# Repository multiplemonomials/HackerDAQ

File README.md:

# HackerDAQ: A Data Acquisition System for Hackers

HackerDAQ is a work-in-progress project to create an open-source data acquisition system. The project is currently in its early stages, but the goal is to create something that can be used in place of industrial DAQ systems to record high-quality data.

## Background and Motivation

The tech industry is in kind of a weird place when it comes to data acquisition (DAQ) systems. Suppose you have some sort of mechanical system you want to work with -- maybe a science experiment, maybe an industrial process, maybe an automation system, who knows. You have some sensors that you need to read and record the data from, and maybe you want to control some outputs as well, like turning the power on to some valves/solenoids/motors in response to a sensor reading. To do this, you need a DAQ system. However, an odd divide exists in the DAQ industry right now, between the incredibly professional and the almost insultingly hobbyist.

At one end of the spectrum, there are industrial-grade offerings from companies like National Instruments, Beckhoff, and Dewesoft. These systems are capable, flexible, and reliable -- but also extremely expensive. Even an entry-level NI system will run you well into the mid 4 figures, and other manufacturers are similar or worse. What if you can't afford that? Well, in many cases, your only option is getting an Arduino or Raspberry Pi and some basic dev boards for the sensors you need, and then hacking together enough software to log the data over serial. I've seen this many times, and while it does sometimes work, by doing it, you give up a lot of niceties like defined accuracy, noise resistance, a constant sample rate, etc.

Meanwhile, technology has moved on, and we're now in an era where highly accurate, multi-input Analog-Digital Converter (ADC) chips can be purchased very cheaply. This project has selected the [AD7770](https://www.analog.com/en/products/ad7770.html) from Analog Devices, a 21-bit, 32kHz, 8-input ADC which can be purchased for about $15 each at quantity. Using this chip enables DAQ devices to be made quite simply and cheaply, as one basically just needs to attach different front-ends to this chip to convert the signals based on the sensor being sampled. With the existence of this chip and others like it, there is really no justification for DAQ devices to cost thousands of dollars unless you need better accuracy or sampling rate than these types of ADCs can provide.

## Basic Overview

The HackerDAQ consists of a main board with a microcontroller on it and basic circuitry such as power supplies, an Ethernet port, and a MicroSD slot. The main board would have a number of connectors for cards to plug in, each of which carries power, GPIOs, and SPI bus signals.

Cards can be designed for many different applications, including digital I/O and many different types of analog sensors. The user can select only the cards they need for the application they have in mind, keeping the base cost of the system down and allowing the user to get exactly the I/O they need. The SPI bus was selected for communications with these cards as it is fast, there are a wide range of chips available that speak it, and it supports bussing together multiple chips on the card over one set of bus lines. In a lot of ways, these cards are similar to existing sensor interconnect systems like SparkFun Qwiic / Adafruit Stemma / Digilent Pmod, where you can buy various task-specific modules and connect them to a motherboard. This would just be focused more on DAQ stuff and be more industrial-grade.

In terms of software, the HackerDAQ would include firmware that would run on the board and interface with all the cards, send data to connected user interface(s), and receive and execute commands. On the PC side, there would be a basic program that can display and record data. For users who don't want to program, they can see the live data in the GUI, record it to a file, and manually control outputs. For users who are a little more comfortable with programming, they could write scripts (likely python) that would run on the host machine and be able to control the DAQ. And for users who have embedded software experience, they could write their own code that extends or replaces the firmware on the actual DAQ!

## Key Decisions

| Area | Decision | Why |
|------------|-------------|--------------|
|Physical architecture | Main board + swappable cards | <ul><li>Avoids need to create multi-function inputs which would increase complexity</li><li>Makes system cheaper if you only need a few types of inputs</li><li>Avoids need to mess around with external amplifiers or other circuitry for sensors that need them -- they can be built directly into the card</li><li>Allows for much wider range of off-the-shelf supported functionality</li></ul>|
|CPU|NXP MCX Alpha Microcontroller running Mbed OS|<ul><li>Using a microcontroller, rather than a linux CPU + supporting circuitry, keeps the cost down</li><li>Using an RTOS rather than a full OS makes microsecond-level timestamping and SPI transaction scheduling possible</li><li>This MCU has two CPU cores at 150 MHz, plus a powerful DMA controller, a fast internal bus, and lots of SPI connectivity</li></ul>|
|SPI bus topology|2 card connectors per SPI bus, one leader card and one follower. All cards on a given bus must share the same polling rate.|<ul><li>MCU does not have enough pins for each of the 8 slots to have its own dedicated SPI bus, so there needs to be some way for cards to share a bus.</li><li>In most real systems, you generally have a lot of sensors at the same data rate, so I do not expect this to be too crippling of a limitation</li></ul>|
|Connection to host|Ethernet, potential upgrade later to add USB|<ul><li>Ethernet provides high quality electrical isolation and is highly noise-immune, so it's great for industrial applications</li><li>Ethernet peripherals in microcontrollers are well-optimized for high data rate applications</li><li>Allows the DAQ to connect to a larger network and interact with multiple machines, plus receive time via NTP</li></ul>|
|Local recording|MicroSD (SPI based)|<ul><li>Important to have a method of locally recording data for standalone applications</li><li>Mbed has a preexisting driver for MicroSD cards in SPI mode</li><li>SDIO mode is faster but driver support is less present (though not totally hopeless either)</li></ul>|
|Card identification|4kiB SPI EEPROM on the card (thinking M95320-RMN6)|<ul><li>Allows SW to largely autoconfigure itself based on the cards that are physically installed</li><li>Provides a convenient place to store calibration data!</li></ul>|
|Card to sensor connectors|Molex Mini-Fit|<ul><li>I have used these connectors in the past and they are really balanced all-around:<ul><li>Retention clip ensures they can't vibrate loose</li><li>Rated for ~8A continuous per pin</li><li>Good size: not so small that they are hard to work with, but not so big that they make your entire system bigger</li></ul></li><li>Big downside is that the crimp tool costs $400. Could mitigate by supplying one wire harness with each card that users can splice their own sensor wires to</li></ul>|
|Card to main board connector|15-pin, 2 row D-Sub (DA-15)|<ul><li>Very cheap</li><li>Screws provide relatively beefy mechanical retention</li><li>Not a size used in consumer hardware so unlikely to be plugged in to, say, a monitor accidentally</li><li>Still uses standard D-sub hardware so it should be possible to get premade cables, crimpers, etc without too much trouble</li></ul>|

## The Main Unit
The main unit contains a high performance MCX Alpha microcontroller with Ethernet, multiple SPI busses, a MicroSD slot, and a number of extra GPIO pins. 

### Data Recording
Both the Ethernet and the MicroSD card are available for recording data. The Ethernet is for livestreaming when you want to view, record, and process data on a PC, while the MicroSD card would be used for simple applications where you just want to record locally, and could also be configured as a backup so that data isn’t lost if the ethernet connection drops out.

### Power
The main unit takes in and regulates power for the HackerDAQ system. It has a DC input which can handle up to 8A at a variable voltage (9-24V). This voltage, referred to as Vsupply, is sent through the connectors into the cards for use as a higher voltage excitation supply when needed. High-current logic rails are provided for cards and attached devices to use -- currently 5V@8A and 3.3V@8A.

### Card Ports
The main unit has four SPI busses. Each SPI bus provides two card ports, a "leader" port and a "follower" port. The leader and follower ports on a given bus can have different cards connected, but *must* operate at the same speed as SPI transactions for all cards will happen at a fixed cycle rate for the bus.

### Expansion Port
Some of the microcontroller I/O pins that are not connected to one of the SPI busses are routed to the expansion port. This will include some digital pins (with I2C/PWM/UART) and some analog pins. Advanced users who are comfortable programming embedded C++ can add write their own software that uses these pins. This allows the HackerDAQ to be used as a jumping-off point for one's own projects!

Also, SWD debug pins and reset pin are broken out to an ARM SWD debug connector, for use with a debug tool like a J-Link or MCU-Link.

### Open Questions
- Is it worth adding a battery-backed RTC so that the time can be maintained if there is a power outage?
- Does PoE support make sense?

### Card Interface
The main unit would provide the following signals to each card:
- SPI signals (MOSI, MISO, SCLK)
- 3x CS lines
    - This allows having 2 addressable chips on the card side, plus the EEPROM
    - 8.192MHz clock signal for the ADC
    - +12V, +5V, and +3.3V digital rails
    - A data ready line from the card
    - A sync line to the card

### Analog Card Basics
Each analog card would contain the same basic DNA:
- Analog front-end, with ESD protection and passive filtering
- Instrumentation amplifier, if needed
- Voltage reference, LTC6658 on cards that need to supply precision excitation voltage, other cheaper option (or built-in ref) if only voltage input is needed
- Multi-input ADC with SPI interface
- SPI EEPROM that stores the card's identity information and calibration

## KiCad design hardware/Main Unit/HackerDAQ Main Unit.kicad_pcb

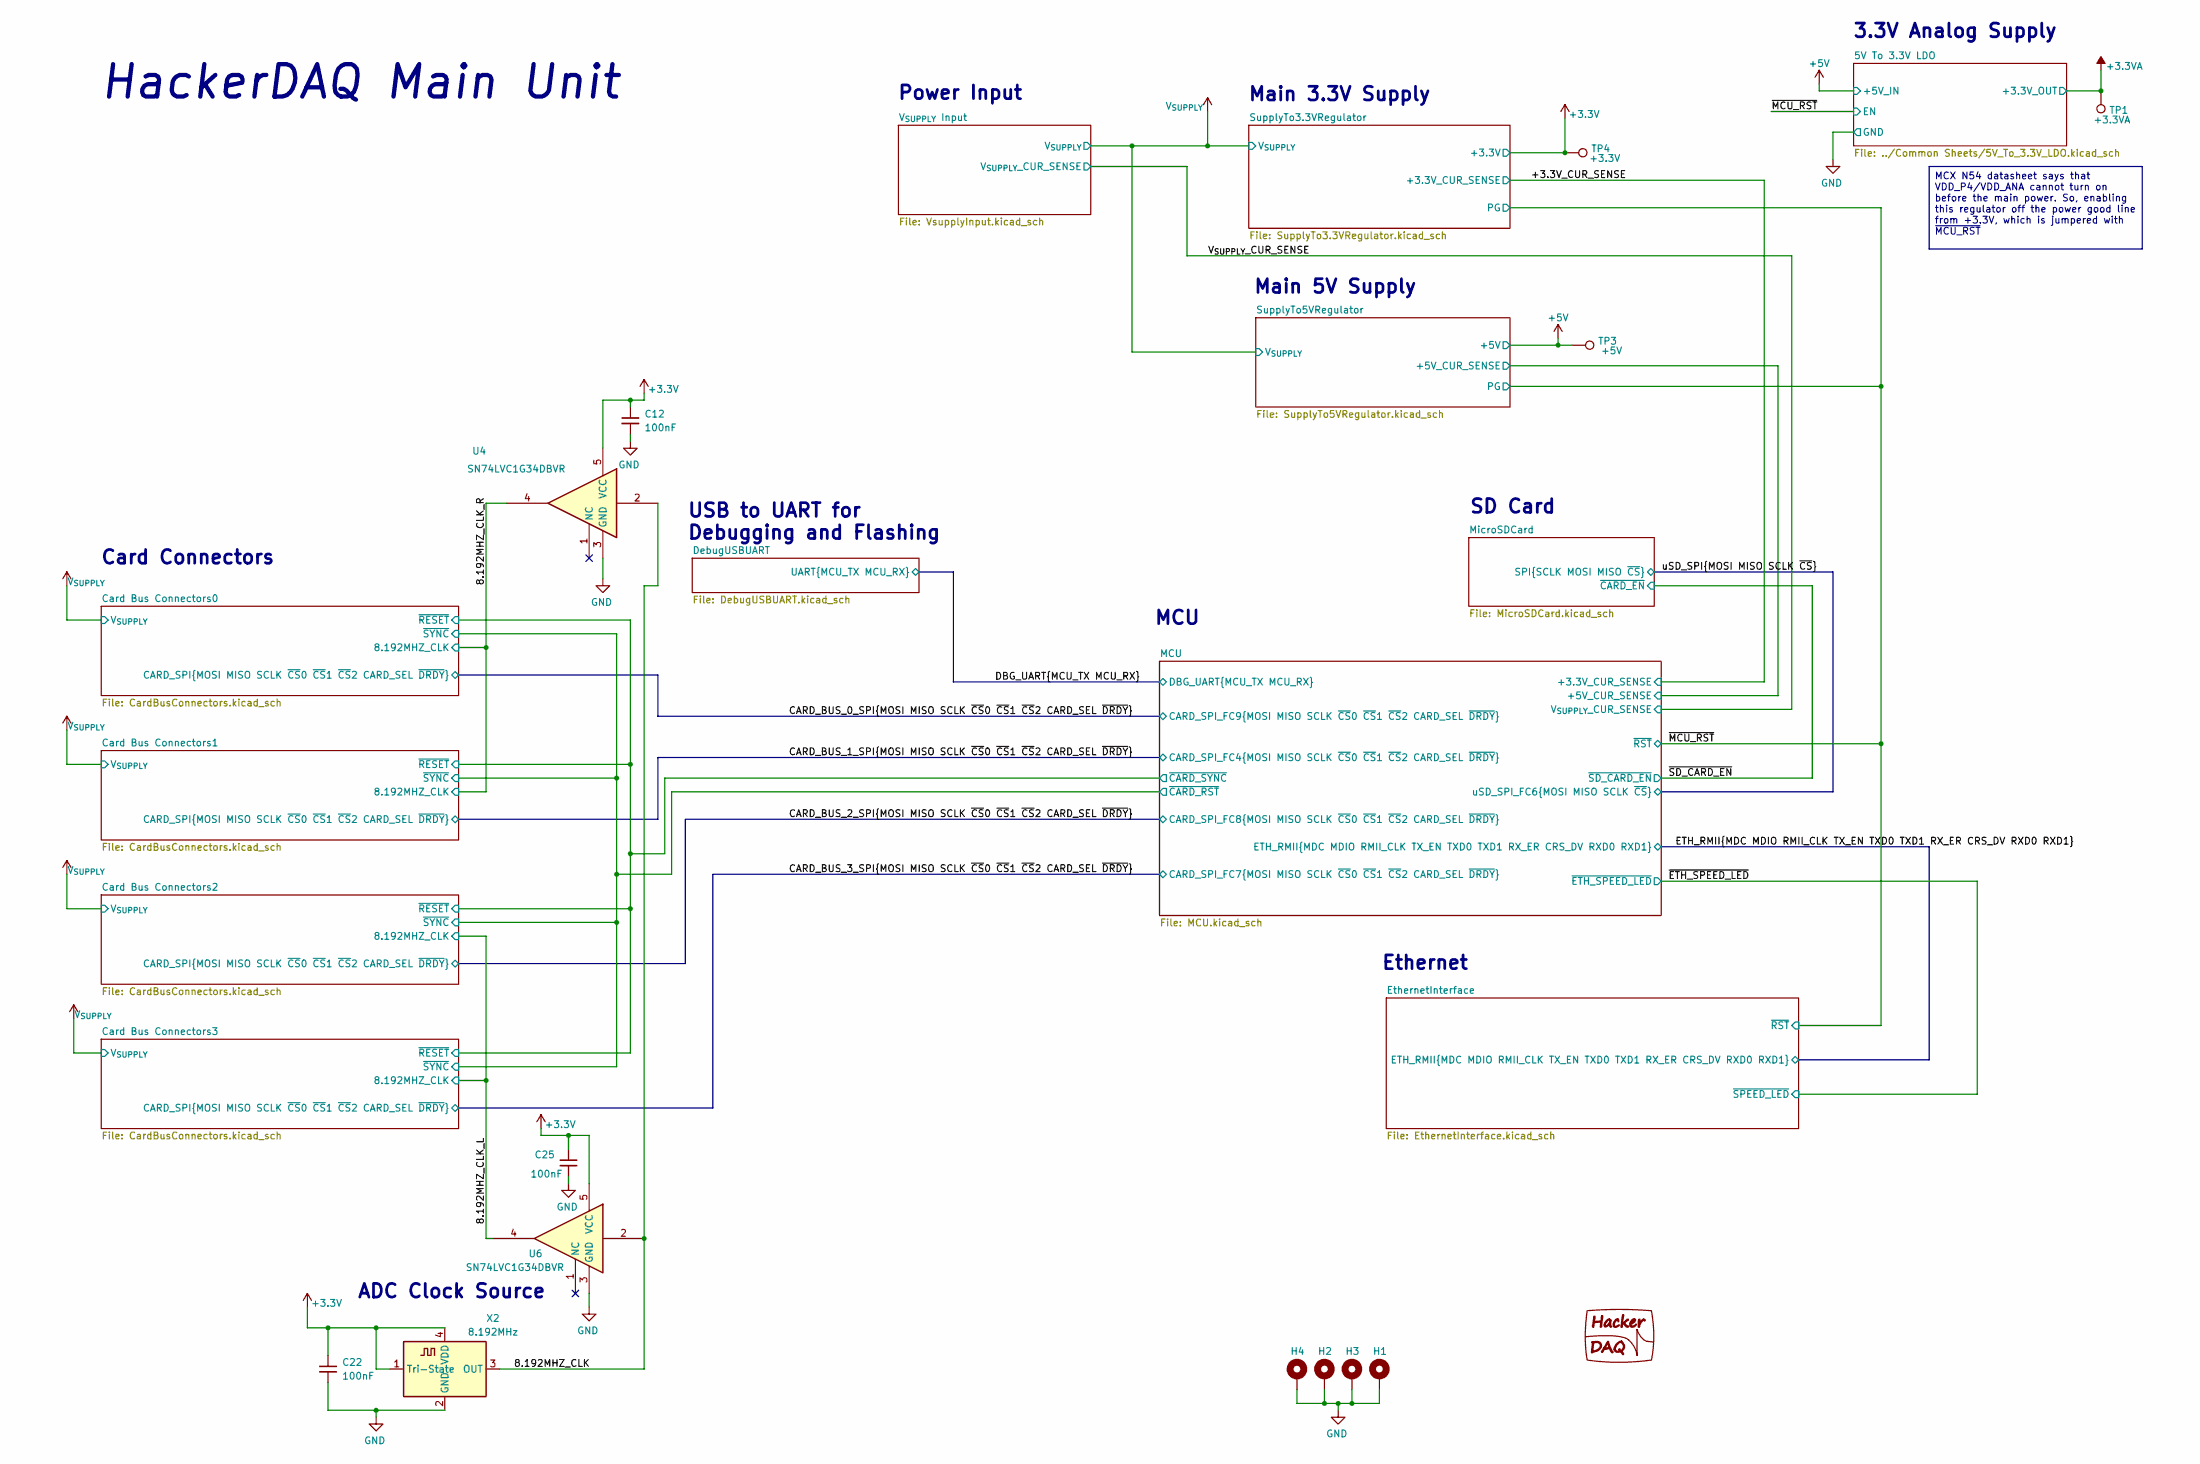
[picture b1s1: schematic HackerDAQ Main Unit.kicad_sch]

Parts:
C12, C22, C25: 100nF; C_0603_1608Metric
H1, H2, H3, H4: MountingHole_Pad; MountingHole_4.3mm_M4_DIN965_Pad
LG1: HackerDAQ Logo
TP1: +3.3VA; TestPoint_THTPad_D2.5mm_Drill1.2mm
TP3: +5V; TestPoint_THTPad_D2.5mm_Drill1.2mm
TP4: +3.3V; TestPoint_THTPad_D2.5mm_Drill1.2mm
U4, U6: SN74LVC1G34DBVR; SOT-23-5
X2: 8.192MHz; Oscillator_SMD_ECS_2520MV-xxx-xx-4Pin_2.5x2.0mm

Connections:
/8.192MHZ_CLK: U4.2, U6.2, X2.3 (OUT)
/8.192MHZ_CLK_L: U6.4; also elsewhere on the board
/8.192MHZ_CLK_R: U4.4; also elsewhere on the board

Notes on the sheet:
ADC Clock Source
HackerDAQ Main Unit
Main 3.3V Supply
MCU
Ethernet
Card Connectors
SD Card
USB to UART for Debugging and Flashing
3.3V Analog Supply
Main 5V Supply
Power Input
MCX N54 datasheet says that VDD_P4/VDD_ANA cannot turn on before the main power. So, enabling this regulator off the power good line from +3.3V, which is jumpered with ~{MCU_RST}

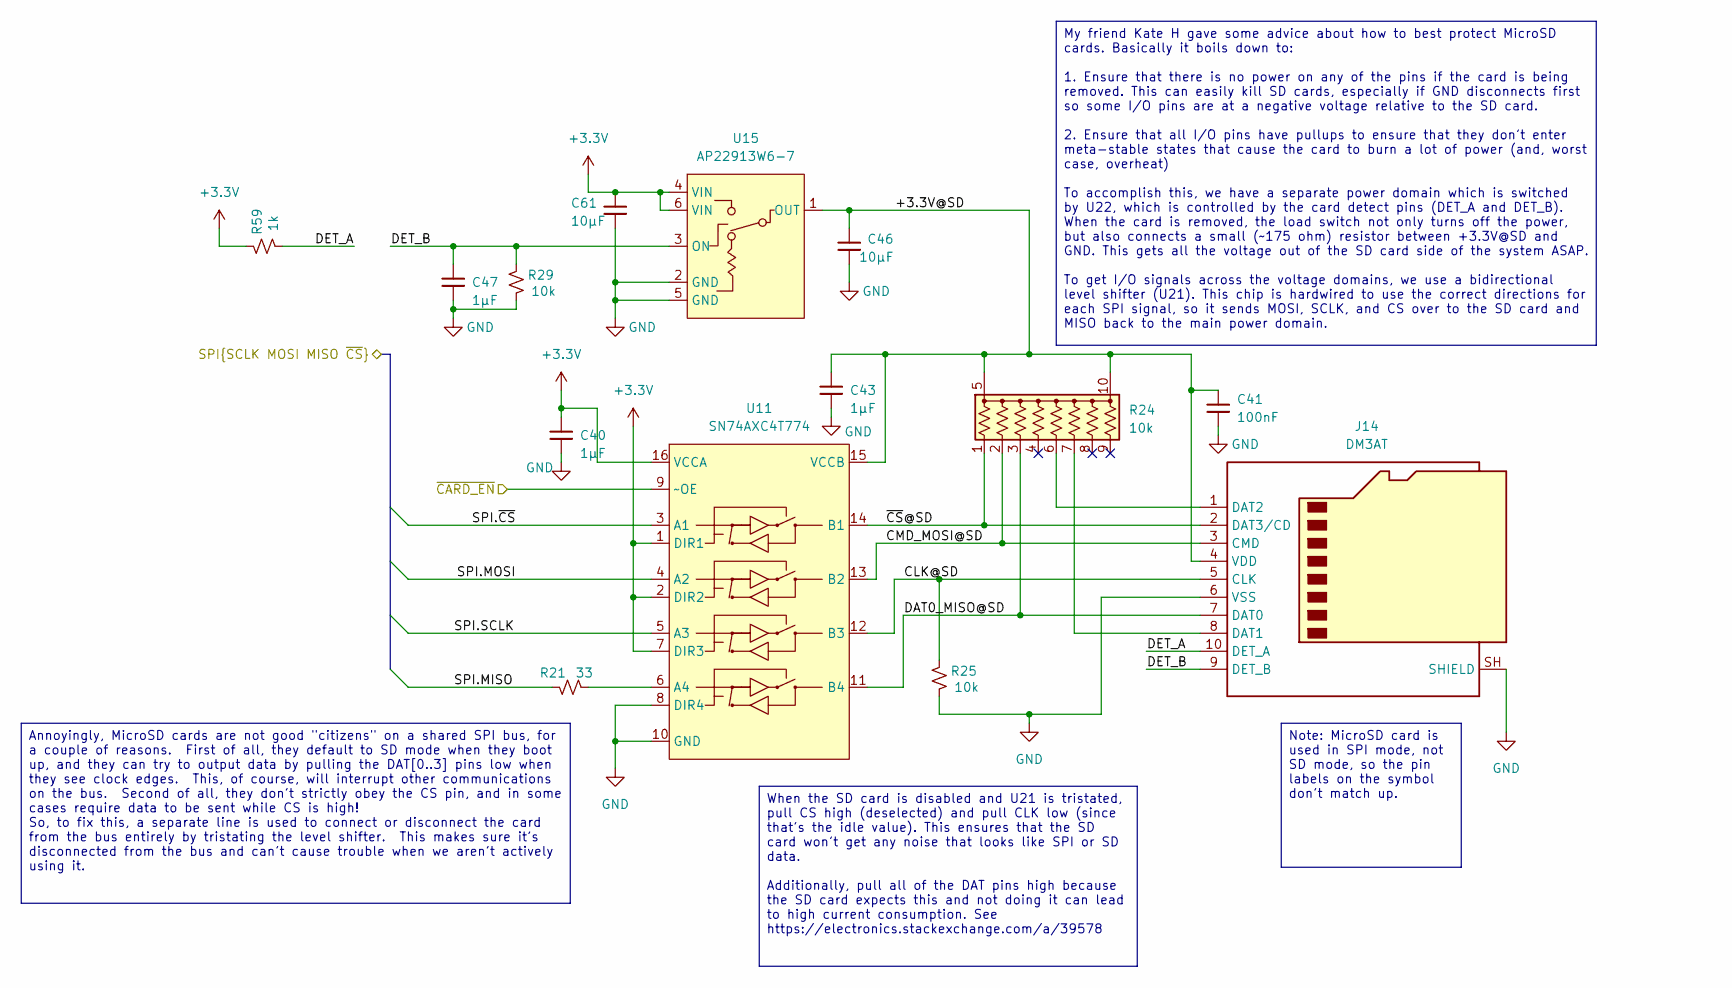
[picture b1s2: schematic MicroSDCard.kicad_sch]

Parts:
C40, C43, C47: 1µF; C_0603_1608Metric
C41: 100nF; C_0603_1608Metric
C46, C61: 10µF; C_1206_3216Metric
J14: DM3AT; microSD_HC_Hirose_DM3AT-SF-PEJM5
R21: 33; R_0603_1608Metric
R24: 10k; CTS 745C101
R25, R29: 10k; R_0603_1608Metric
R59: 1k; R_0603_1608Metric
U11: SN74AXC4T774; TSSOP-16_4.4x5mm_P0.65mm
U15: AP22913W6-7; SOT-23-6

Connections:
/MicroSDCard/+3.3V@SD: C41.1, C43.1, C46.2, J14.4 (VDD), R24.5 (common), R24.10 (common), U11.15 (VCCB), U15.1 (OUT)
/MicroSDCard/CLK@SD: J14.5 (CLK), R25.2, U11.12 (B3)
/MicroSDCard/CMD_MOSI@SD: J14.3 (CMD), R24.2 (R2), U11.13 (B2)
/MicroSDCard/DAT0_MISO@SD: J14.7 (DAT0), R24.3 (R3), U11.11 (B4)
/MicroSDCard/DET_A: J14.10 (DET_A), R59.1
/MicroSDCard/DET_B: C47.1, J14.9 (DET_B), R29.2, U15.3 (ON)
/MicroSDCard/~CS@SD: J14.2 (DAT3/CD), R24.1 (R1), U11.14 (B1)
/uSD_SPI.MISO: R21.1; also elsewhere on the board
/uSD_SPI.MOSI: U11.4 (A2); also elsewhere on the board
/uSD_SPI.SCLK: U11.5 (A3); also elsewhere on the board
/uSD_SPI.~CS: U11.3 (A1); also elsewhere on the board
/~SD_CARD_EN: U11.9 (~OE); also elsewhere on the board
unnamed: J14.8 (DAT1), R24.7 (R6)
unnamed: J14.1 (DAT2), R24.6 (R5)
unnamed: R21.2, U11.6 (A4)

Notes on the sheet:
Note: MicroSD card is used in SPI mode, not SD mode, so the pin labels on the symbol don't match up.
When the SD card is disabled and U21 is tristated, pull CS high (deselected) and pull CLK low (since that's the idle value). This ensures that the SD card won't get any noise that looks like SPI or SD data. Additionally, pull all of the DAT pins high because the SD card expects this and not doing i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
My friend Kate H gave some advice about how to best protect MicroSD cards. Basically it boils down to: 1. Ensure that there is no power on any of the pins if the card is being removed. This can easily kill SD cards, especially if GND disconnects first so some I/O pins are at a negative voltage rela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
Annoyingly, MicroSD cards are not good "citizens" on a shared SPI bus, for a couple of reasons. First of all, they default to SD mode when they boot up, and they can try to output data by pulling the DAT[0..3] pins low when they see clock edges. This, of course, will interrupt other communications 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

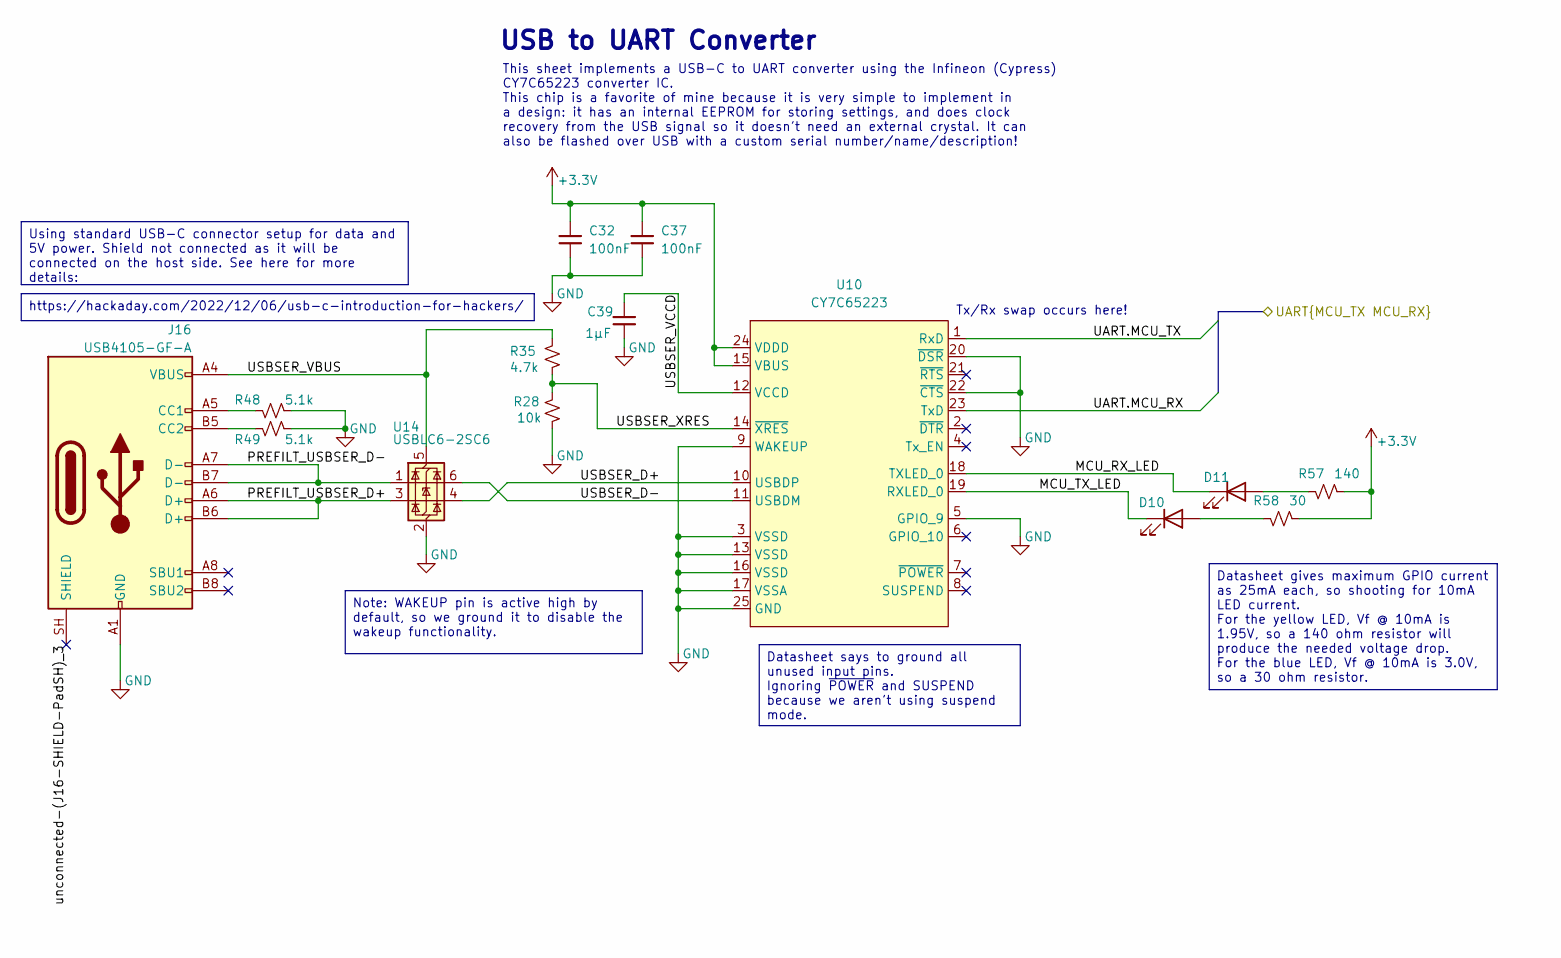
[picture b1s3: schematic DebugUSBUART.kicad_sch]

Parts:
C32, C37: 100nF; C_0603_1608Metric
C39: 1µF; C_0603_1608Metric
D10: AA3528QBS; AA3528
D11: AA3528SYSK; AA3528
J16: USB4105-GF-A; USB_C_Receptacle_GCT_USB4105-xx-A_16P_TopMnt_Horizontal-Ext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
R28: 10k; R_0603_1608Metric
R35: 4.7k; R_0603_1608Metric
R48, R49: 5.1k; R_0603_1608Metric
R57: 140; R_0603_1608Metric
R58: 30; R_0603_1608Metric
U10: CY7C65223; QFN-24-1EP_4x4mm_P0.5mm_EP2.65x2.65mm-LengthenedPads
U14: USBLC6-2SC6; SOT-23-6

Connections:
/DBG_UART.MCU_RX: U10.23 (TxD); also elsewhere on the board
/DBG_UART.MCU_TX: U10.1 (RxD); also elsewhere on the board
/DebugUSBUART/MCU_RX_LED: D11.1 (K), U10.18 (TXLED_0)
/DebugUSBUART/MCU_TX_LED: D10.1 (K), U10.19 (RXLED_0)
/DebugUSBUART/PREFILT_USBSER_D+: J16.A6 (D+), J16.B6 (D+), U14.3 (I/O2)
/DebugUSBUART/PREFILT_USBSER_D-: J16.A7 (D-), J16.B7 (D-), U14.1 (I/O1)
/DebugUSBUART/USBSER_D+: U10.10 (USBDP), U14.4 (I/O2)
/DebugUSBUART/USBSER_D-: U10.11 (USBDM), U14.6 (I/O1)
/DebugUSBUART/USBSER_VBUS: J16.A4 (VBUS), J16.A9 (VBUS), J16.B4 (VBUS), J16.B9 (VBUS), R35.2, U14.5 (VBUS)
/DebugUSBUART/USBSER_VCCD: C39.1, U10.12 (VCCD)
/DebugUSBUART/USBSER_XRES: R28.2, R35.1, U10.14 (~XRES)
/DebugUSBUART/unconnected-(J16-SHIELD-PadSH)_3: J16.SH (SHIELD)
/DebugUSBUART/unconnected-(J16-SHIELD-PadSH)_3_1: J16.SH (SHIELD)
/DebugUSBUART/unconnected-(J16-SHIELD-PadSH)_3_2: J16.SH (SHIELD)
/DebugUSBUART/unconnected-(J16-SHIELD-PadSH)_3_3: J16.SH (SHIELD)
unnamed: D10.2 (A), R58.2
unnamed: D11.2 (A), R57.2
unnamed: J16.A5 (CC1), R48.2
unnamed: J16.B5 (CC2), R49.2

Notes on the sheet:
This sheet implements a USB-C to UART converter using the Infineon (Cypress) CY7C65223 converter IC. This chip is a favorite of mine because it is very simple to implement in a design: it has an internal EEPROM for storing settings, and does clock recovery from the USB signal so it doesn't need an 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
USB to UART Converter
Tx/Rx swap occurs here!
Datasheet says to ground all unused input pins. Ignoring ~{POWER} and SUSPEND because we aren't using suspend mode.
https://hackaday.com/2022/12/06/usb-c-introduction-for-hackers/
Datasheet gives maximum GPIO current as 25mA each, so shooting for 10mA LED current. For the yellow LED, Vf @ 10mA is 1.95V, so a 140 ohm resistor will produce the needed voltage drop. For the blue LED, Vf @ 10mA is 3.0V, so a 30 ohm resistor.
Note: WAKEUP pin is active high by default, so we ground it to disable the wakeup functionality.
Using standard USB-C connector setup for data and 5V power. Shield not connected as it will be connected on the host side. See here for more details:

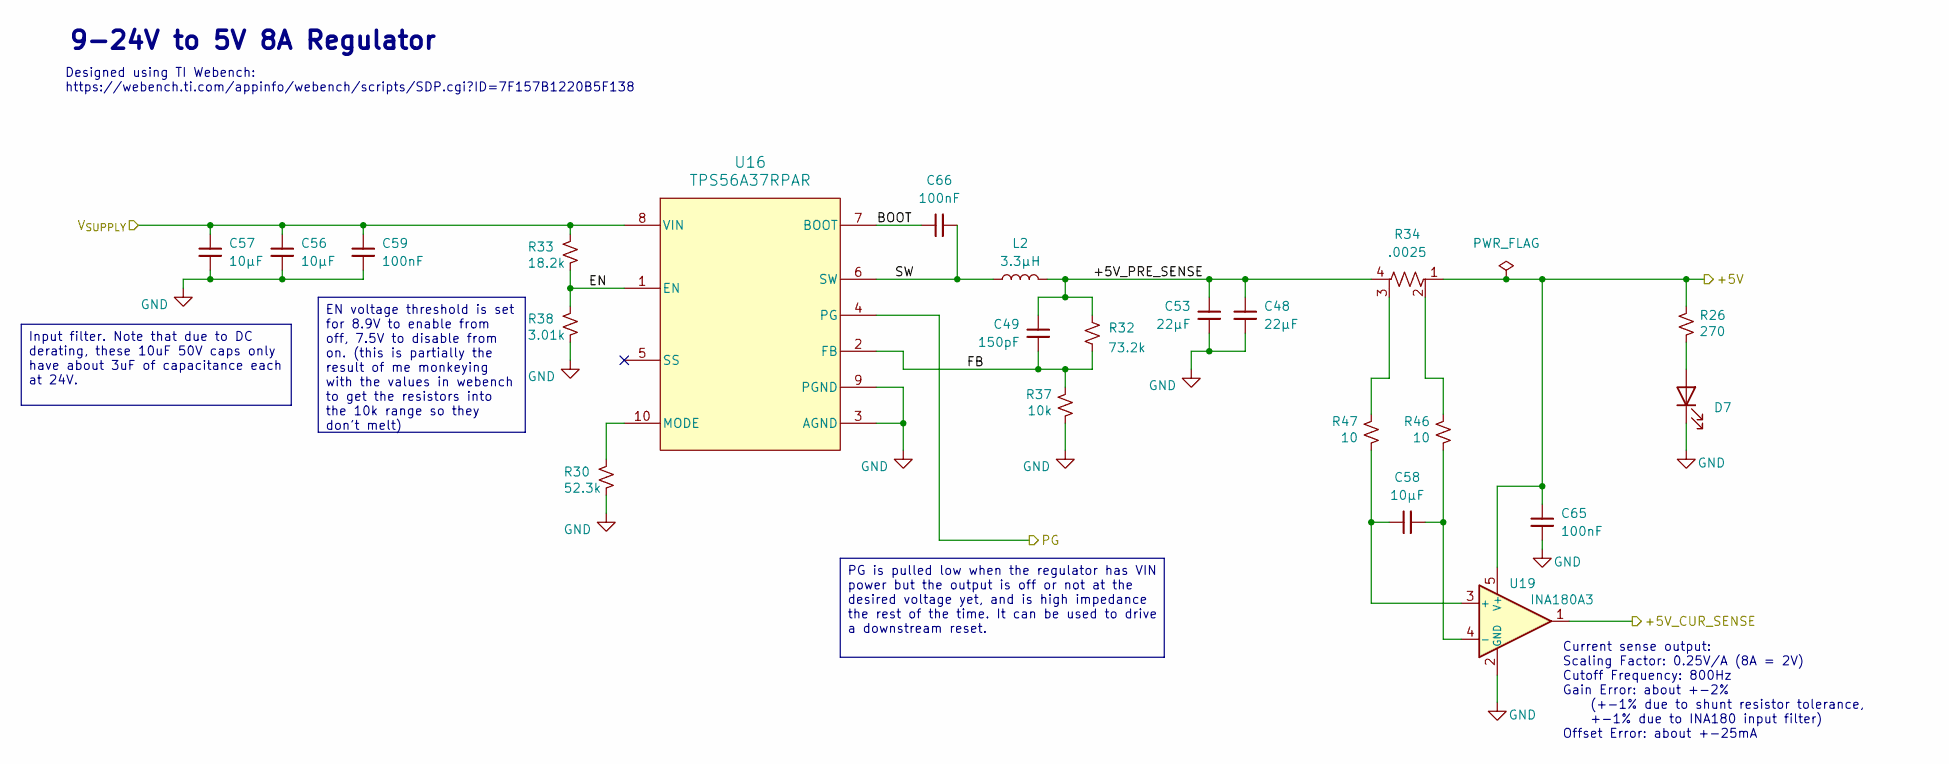
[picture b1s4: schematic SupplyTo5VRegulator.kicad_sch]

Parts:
C48, C53: 22µF; C_1210_3225Metric
C49: 150pF; C_0603_1608Metric
C56, C57: 10µF; C_1210_3225Metric
C58: 10µF; C_1206_3216Metric
C59, C65, C66: 100nF; C_0603_1608Metric
D7: AA3528CGSK; AA3528
L2: 3.3μH; L_Vishay_IHLP-3232
R26: 270; R_0603_1608Metric
R30: 52.3k; R_0603_1608Metric
R32: 73.2k; R_0603_1608Metric
R33: 18.2k; R_0603_1608Metric
R34: .0025; D1FCP0612
R37: 10k; R_0603_1608Metric
R38: 3.01k; R_0603_1608Metric
R46, R47: 10; R_0603_1608Metric
U16: TPS56A37RPAR; RPA0010A-MFG
U19: INA180A3; SOT-23-5

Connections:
/MCU/+5V_CUR_SENSE: U19.1; also elsewhere on the board
/SupplyTo5VRegulator/+5V_PRE_SENSE: C48.2, C49.2, C53.2, L2.2, R32.2, R34.4
/SupplyTo5VRegulator/BOOT: C66.1, U16.7 (BOOT)
/SupplyTo5VRegulator/EN: R33.1, R38.2, U16.1 (EN)
/SupplyTo5VRegulator/FB: C49.1, R32.1, R37.1, U16.2 (FB)
/SupplyTo5VRegulator/SW: C66.2, L2.1, U16.6 (SW)
/~MCU_RST: U16.4 (PG); also elsewhere on the board
unnamed: D7.2 (A), R26.1
unnamed: R34.2, R46.1
unnamed: R34.3, R47.1
unnamed: R30.2, U16.10 (MODE)
unnamed: C58.2, R47.2, U19.3 (+)
unnamed: C58.1, R46.2, U19.4 (-)
V_{SUPPLY}: C56.2, C57.2, C59.1, R33.2, U16.8 (VIN); also elsewhere on the board

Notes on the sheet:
Designed using TI Webench: https://webench.ti.com/appinfo/webench/scripts/SDP.cgi?ID=7F157B1220B5F138
9-24V to 5V 8A Regulator
Current sense output: Scaling Factor: 0.25V/A (8A = 2V) Cutoff Frequency: 800Hz Gain Error: about +-2% (+-1% due to shunt resistor tolerance, +-1% due to INA180 input filter) Offset Error: about +-25mA
EN voltage threshold is set for 8.9V to enable from off, 7.5V to disable from on. (this is partially the result of me monkeying with the values in webench to get the resistors into the 10k range so they don't melt)
Input filter. Note that due to DC derating, these 10uF 50V caps only have about 3uF of capacitance each at 24V.
PG is pulled low when the regulator has VIN power but the output is off or not at the desired voltage yet, and is high impedance the rest of the time. It can be used to drive a downstream reset.

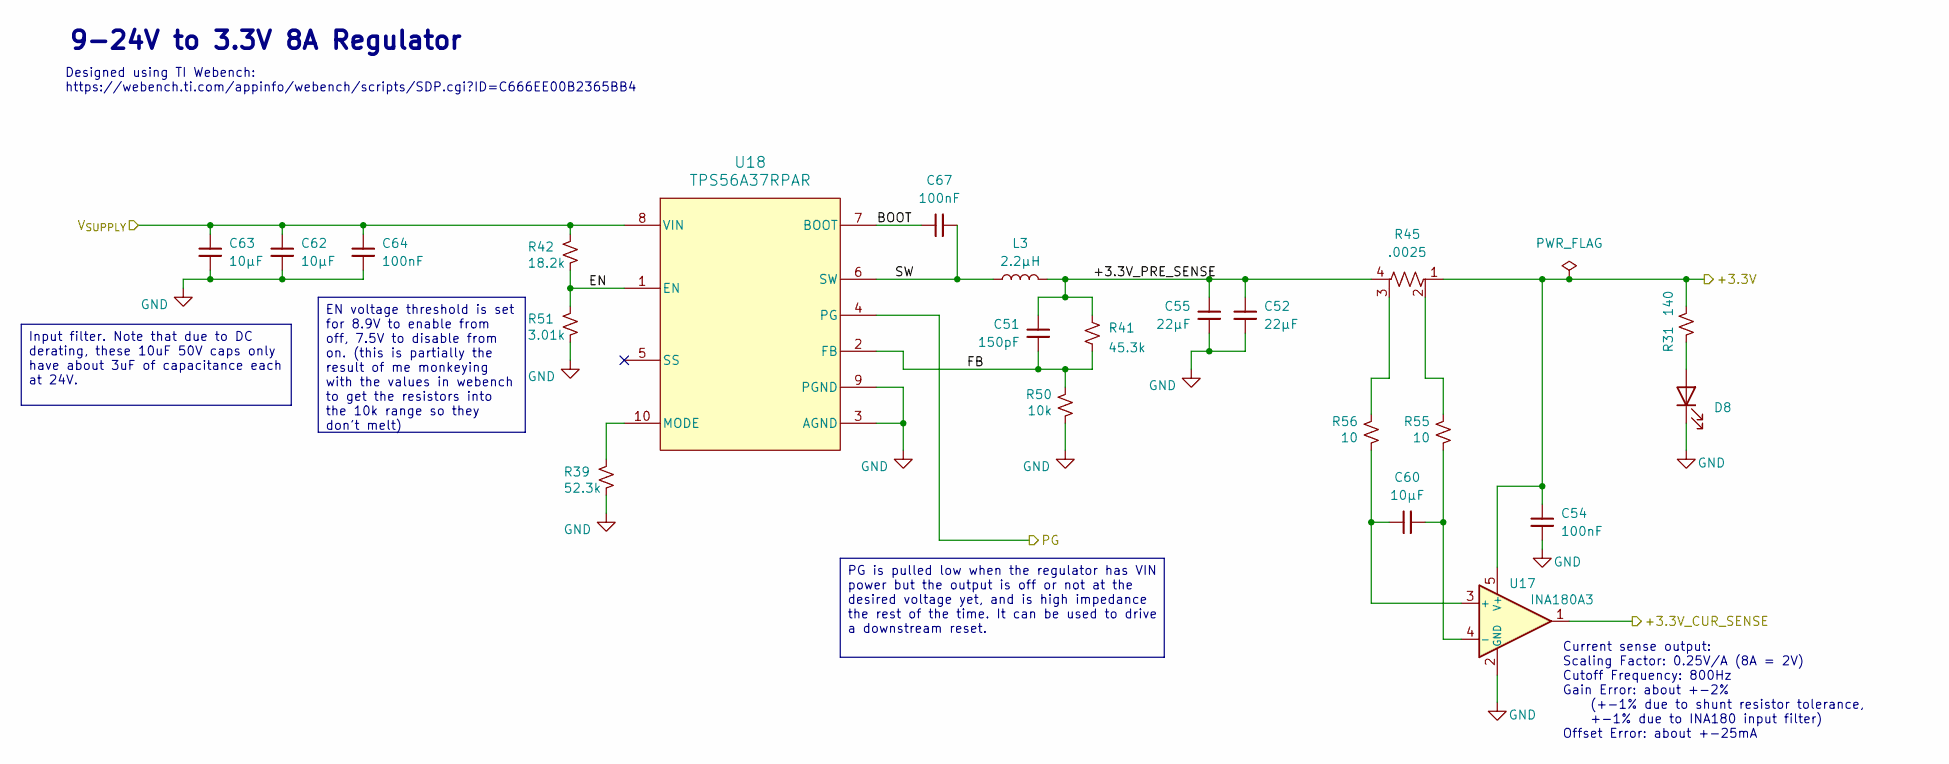
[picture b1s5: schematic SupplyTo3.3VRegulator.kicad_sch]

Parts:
C51: 150pF; C_0603_1608Metric
C52, C55: 22µF; C_1210_3225Metric
C54, C64, C67: 100nF; C_0603_1608Metric
C60: 10µF; C_1206_3216Metric
C62, C63: 10µF; C_1210_3225Metric
D8: AA3528CGSK; AA3528
L3: 2.2μH; 0630CDMCDDS
R31: 140; R_0603_1608Metric
R39: 52.3k; R_0603_1608Metric
R41: 45.3k; R_0603_1608Metric
R42: 18.2k; R_0603_1608Metric
R45: .0025; D1FCP0612
R50: 10k; R_0603_1608Metric
R51: 3.01k; R_0603_1608Metric
R55, R56: 10; R_0603_1608Metric
U17: INA180A3; SOT-23-5
U18: TPS56A37RPAR; RPA0010A-MFG

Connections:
/+3.3V_CUR_SENSE: U17.1; also elsewhere on the board
/SupplyTo3.3VRegulator/+3.3V_PRE_SENSE: C51.2, C52.2, C55.2, L3.2, R41.2, R45.4
/SupplyTo3.3VRegulator/BOOT: C67.1, U18.7 (BOOT)
/SupplyTo3.3VRegulator/EN: R42.1, R51.2, U18.1 (EN)
/SupplyTo3.3VRegulator/FB: C51.1, R41.1, R50.1, U18.2 (FB)
/SupplyTo3.3VRegulator/SW: C67.2, L3.1, U18.6 (SW)
/~MCU_RST: U18.4 (PG); also elsewhere on the board
unnamed: D8.2 (A), R31.2
unnamed: R45.2, R55.1
unnamed: R45.3, R56.1
unnamed: C60.2, R56.2, U17.3 (+)
unnamed: C60.1, R55.2, U17.4 (-)
unnamed: R39.2, U18.10 (MODE)
V_{SUPPLY}: C62.2, C63.2, C64.1, R42.2, U18.8 (VIN); also elsewhere on the board

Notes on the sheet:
Designed using TI Webench: https://webench.ti.com/appinfo/webench/scripts/SDP.cgi?ID=C666EE00B2365BB4
Current sense output: Scaling Factor: 0.25V/A (8A = 2V) Cutoff Frequency: 800Hz Gain Error: about +-2% (+-1% due to shunt resistor tolerance, +-1% due to INA180 input filter) Offset Error: about +-25mA
9-24V to 3.3V 8A Regulator
PG is pulled low when the regulator has VIN power but the output is off or not at the desired voltage yet, and is high impedance the rest of the time. It can be used to drive a downstream reset.
EN voltage threshold is set for 8.9V to enable from off, 7.5V to disable from on. (this is partially the result of me monkeying with the values in webench to get the resistors into the 10k range so they don't melt)
Input filter. Note that due to DC derating, these 10uF 50V caps only have about 3uF of capacitance each at 24V.

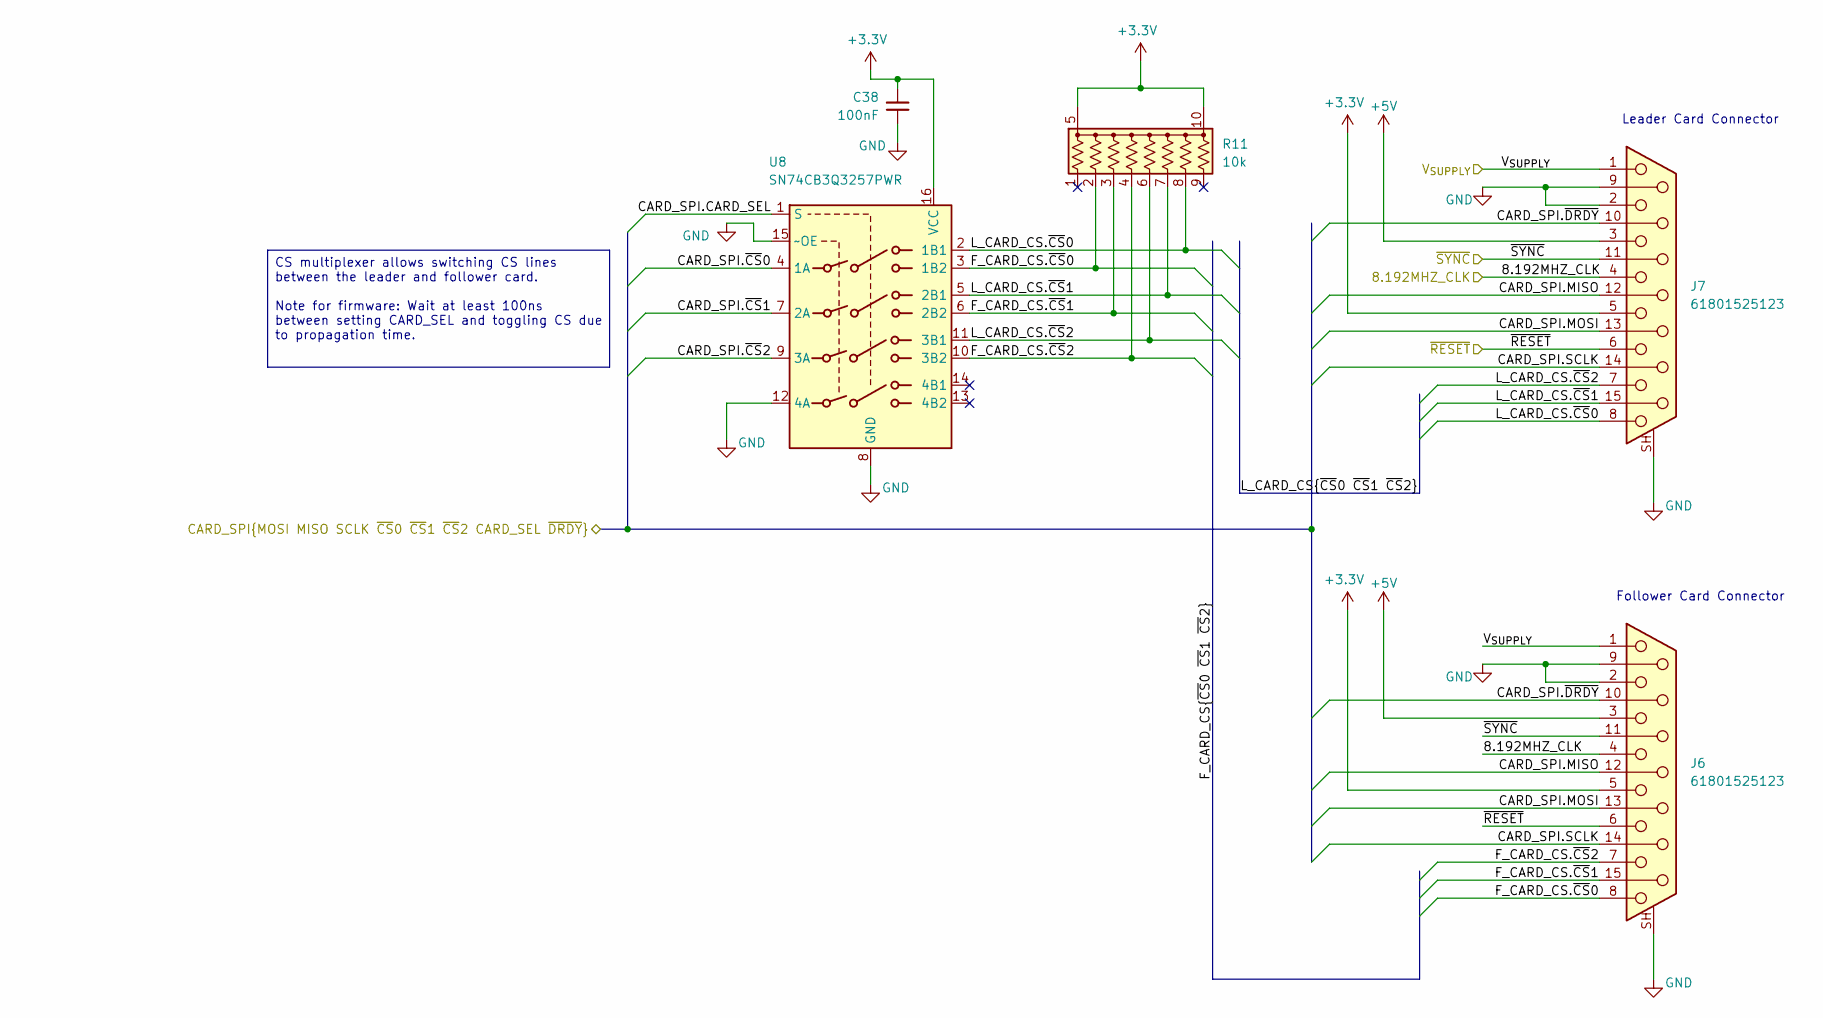
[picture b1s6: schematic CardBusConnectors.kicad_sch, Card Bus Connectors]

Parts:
C38: 100nF; C_0603_1608Metric
J6, J7: 61801525123; Wurth_61801525123
R11: 10k; CTS 745C101
U8: SN74CB3Q3257PWR; TSSOP-16_4.4x5mm_P0.65mm

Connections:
/8.192MHZ_CLK_R: J6.4, J7.4; also elsewhere on the board
/CARD_BUS_1_SPI.CARD_SEL: U8.1 (S); also elsewhere on the board
/CARD_BUS_1_SPI.MISO: J6.12, J7.12; also elsewhere on the board
/CARD_BUS_1_SPI.MOSI: J6.13, J7.13; also elsewhere on the board
/CARD_BUS_1_SPI.SCLK: J6.14, J7.14; also elsewhere on the board
/CARD_BUS_1_SPI.~CS0: U8.4 (1A); also elsewhere on the board
/CARD_BUS_1_SPI.~CS1: U8.7 (2A); also elsewhere on the board
/CARD_BUS_1_SPI.~CS2: U8.9 (3A); also elsewhere on the board
/CARD_BUS_1_SPI.~DRDY: J6.10, J7.10; also elsewhere on the board
/Card Bus Connectors0/~RESET: J6.6, J7.6; also elsewhere on the board
/Card Bus Connectors0/~SYNC: J6.11 (P111), J7.11 (P111); also elsewhere on the board
/Card Bus Connectors1/F_CARD_CS.~CS0: J6.8, R11.2 (R2), U8.3 (1B2)
/Card Bus Connectors1/F_CARD_CS.~CS1: J6.15, R11.3 (R3), U8.6 (2B2)
/Card Bus Connectors1/F_CARD_CS.~CS2: J6.7, R11.4 (R4), U8.10 (3B2)
/Card Bus Connectors1/L_CARD_CS.~CS0: J7.8, R11.8 (R7), U8.2 (1B1)
/Card Bus Connectors1/L_CARD_CS.~CS1: J7.15, R11.7 (R6), U8.5 (2B1)
/Card Bus Connectors1/L_CARD_CS.~CS2: J7.7, R11.6 (R5), U8.11 (3B1)
V_{SUPPLY}: J6.1, J7.1; also elsewhere on the board

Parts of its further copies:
C1, C2, C30: 100nF; C_0603_1608Metric
J2, J3, J4, J5, J8, J9: 61801525123; Wurth_61801525123
R10, R12, R13: 10k; CTS 745C101
U1, U3, U9: SN74CB3Q3257PWR; TSSOP-16_4.4x5mm_P0.65mm

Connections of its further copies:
/8.192MHZ_CLK_L: J2.4, J3.4, J4.4, J5.4; also elsewhere on the board
/8.192MHZ_CLK_R: J8.4, J9.4; also elsewhere on the board
/CARD_BUS_0_SPI.CARD_SEL: U3.1 (S); also elsewhere on the board
/CARD_BUS_0_SPI.MISO: J8.12, J9.12; also elsewhere on the board
/CARD_BUS_0_SPI.MOSI: J8.13, J9.13; also elsewhere on the board
/CARD_BUS_0_SPI.SCLK: J8.14, J9.14; also elsewhere on the board
/CARD_BUS_0_SPI.~CS0: U3.4 (1A); also elsewhere on the board
/CARD_BUS_0_SPI.~CS1: U3.7 (2A); also elsewhere on the board
/CARD_BUS_0_SPI.~CS2: U3.9 (3A); also elsewhere on the board
/CARD_BUS_0_SPI.~DRDY: J8.10, J9.10; also elsewhere on the board
/CARD_BUS_2_SPI.CARD_SEL: U1.1 (S); also elsewhere on the board
/CARD_BUS_2_SPI.MISO: J4.12, J5.12; also elsewhere on the board
/CARD_BUS_2_SPI.MOSI: J4.13, J5.13; also elsewhere on the board
/CARD_BUS_2_SPI.SCLK: J4.14, J5.14; also elsewhere on the board
/CARD_BUS_2_SPI.~CS0: U1.4 (1A); also elsewhere on the board
/CARD_BUS_2_SPI.~CS1: U1.7 (2A); also elsewhere on the board
/CARD_BUS_2_SPI.~CS2: U1.9 (3A); also elsewhere on the board
/CARD_BUS_2_SPI.~DRDY: J4.10, J5.10; also elsewhere on the board
/CARD_BUS_3_SPI.CARD_SEL: U9.1 (S); also elsewhere on the board
/CARD_BUS_3_SPI.MISO: J2.12, J3.12; also elsewhere on the board
/CARD_BUS_3_SPI.MOSI: J2.13, J3.13; also elsewhere on the board
/CARD_BUS_3_SPI.SCLK: J2.14, J3.14; also elsewhere on the board
/CARD_BUS_3_SPI.~CS0: U9.4 (1A); also elsewhere on the board
/CARD_BUS_3_SPI.~CS1: U9.7 (2A); also elsewhere on the board
/CARD_BUS_3_SPI.~CS2: U9.9 (3A); also elsewhere on the board
/CARD_BUS_3_SPI.~DRDY: J2.10, J3.10; also elsewhere on the board
/Card Bus Connectors0/F_CARD_CS.~CS0: J8.8, R10.2 (R2), U3.3 (1B2)
/Card Bus Connectors0/F_CARD_CS.~CS1: J8.15, R10.3 (R3), U3.6 (2B2)
/Card Bus Connectors0/F_CARD_CS.~CS2: J8.7, R10.4 (R4), U3.10 (3B2)
/Card Bus Connectors0/L_CARD_CS.~CS0: J9.8, R10.8 (R7), U3.2 (1B1)
/Card Bus Connectors0/L_CARD_CS.~CS1: J9.15, R10.7 (R6), U3.5 (2B1)
/Card Bus Connectors0/L_CARD_CS.~CS2: J9.7, R10.6 (R5), U3.11 (3B1)
/Card Bus Connectors0/~RESET: J2.6, J3.6, J4.6, J5.6, J8.6, J9.6; also elsewhere on the board
/Card Bus Connectors0/~SYNC: J2.11 (P111), J3.11 (P111), J4.11 (P111), J5.11 (P111), J8.11 (P111), J9.11 (P111); also elsewhere on the board
/Card Bus Connectors2/F_CARD_CS.~CS0: J4.8, R13.2 (R2), U1.3 (1B2)
/Card Bus Connectors2/F_CARD_CS.~CS1: J4.15, R13.3 (R3), U1.6 (2B2)
/Card Bus Connectors2/F_CARD_CS.~CS2: J4.7, R13.4 (R4), U1.10 (3B2)
/Card Bus Connectors2/L_CARD_CS.~CS0: J5.8, R13.8 (R7), U1.2 (1B1)
/Card Bus Connectors2/L_CARD_CS.~CS1: J5.15, R13.7 (R6), U1.5 (2B1)
/Card Bus Connectors2/L_CARD_CS.~CS2: J5.7, R13.6 (R5), U1.11 (3B1)
/Card Bus Connectors3/F_CARD_CS.~CS0: J2.8, R12.2 (R2), U9.3 (1B2)
/Card Bus Connectors3/F_CARD_CS.~CS1: J2.15, R12.3 (R3), U9.6 (2B2)
/Card Bus Connectors3/F_CARD_CS.~CS2: J2.7, R12.4 (R4), U9.10 (3B2)
/Card Bus Connectors3/L_CARD_CS.~CS0: J3.8, R12.8 (R7), U9.2 (1B1)
/Card Bus Connectors3/L_CARD_CS.~CS1: J3.15, R12.7 (R6), U9.5 (2B1)
/Card Bus Connectors3/L_CARD_CS.~CS2: J3.7, R12.6 (R5), U9.11 (3B1)
V_{SUPPLY}: J2.1, J3.1, J4.1, J5.1, J8.1, J9.1; also elsewhere on the board

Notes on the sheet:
Leader Card Connector
Follower Card Connector
CS multiplexer allows switching CS lines between the leader and follower card. Note for firmware: Wait at least 100ns between setting CARD_SEL and toggling CS due to propagation time.
